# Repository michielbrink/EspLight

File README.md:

# EspLight
https://tkkrlab.nl/wiki/Esp-12_led_strip_controller

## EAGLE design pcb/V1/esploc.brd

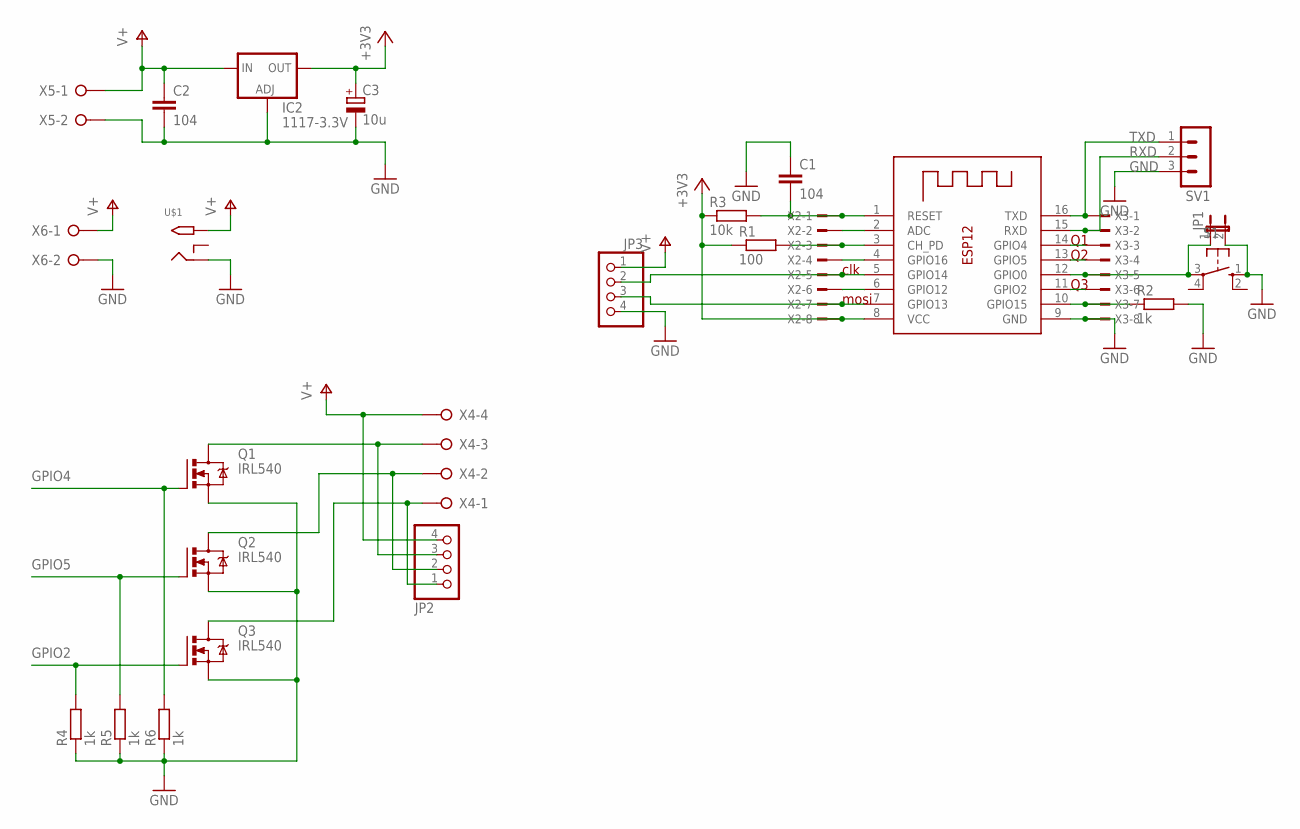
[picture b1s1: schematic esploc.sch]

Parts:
C1, C2: 104; C025_050-025X075
C3: 10u; E2,5-6E
IC2: 1117-3.3V; SOT223
JP1: JP1E; JP1
JP2, JP3: PINHD-1X4; 1X04
Q1, Q2, Q3: IRL540; TO220BV
R1: 100; M0805
R2, R4, R5, R6: 1k; M0805
R3: 10k; M0805
S1: 40-XX; B3F-40XX
SV1: MA03-1
U$1: 2.1MMJACKTHM; PJ-102A
X1: ESP-12
X2, X3: TSW-108-02-S-S
X4: W237-04P; W237-4P
X5, X6: W237-02P; W237-132

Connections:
+3V3: C3.+, IC2.2 (OUT), IC2.4 (OUT), R1.1, R3.1, X1.8 (VCC), X2.8
GND: C1.1, C2.2, C3.-, IC2.1 (ADJ), JP1.2, JP3.4, Q1.S, Q2.S, Q3.S, R2.2, R4.1, R5.1, R6.1, S1.1 (S), SV1.3, U$1.RING, X1.9 (GND), X3.8, X5.2, X6.2
GPIO2: Q3.G, R4.2, X1.11 (GPIO2), X3.6
GPIO4: Q1.G, R6.2, X1.14 (GPIO4), X3.3
GPIO5: Q2.G, R5.2, X1.13 (GPIO5), X3.4
GPIO12: X1.6 (GPIO12), X2.6
GPIO13: JP3.3, X1.7 (GPIO13), X2.7
GPIO14: JP3.2, X1.5 (GPIO14), X2.5
unnamed: C1.2, R3.2, X1.1 (RESET), X2.1
unnamed: R1.2, X1.3 (CH_PD), X2.3
unnamed: R2.1, X1.10 (GPIO15), X3.7
unnamed: X1.4 (GPIO16), X2.4
unnamed: JP1.1, S1.3, X1.12 (GPIO0), X3.5
unnamed: X1.2 (ADC), X2.2
unnamed: JP2.3, Q1.D, X4.3
unnamed: JP2.2, Q2.D, X4.2
unnamed: JP2.1, Q3.D, X4.1
RXD: SV1.2, X1.15 (RXD), X3.2
TXD: SV1.1, X1.16 (TXD), X3.1
V+: C2.1, IC2.3 (IN), JP2.4, JP3.1, U$1.TIP, X4.4, X5.1, X6.1

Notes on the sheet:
clk
mosi

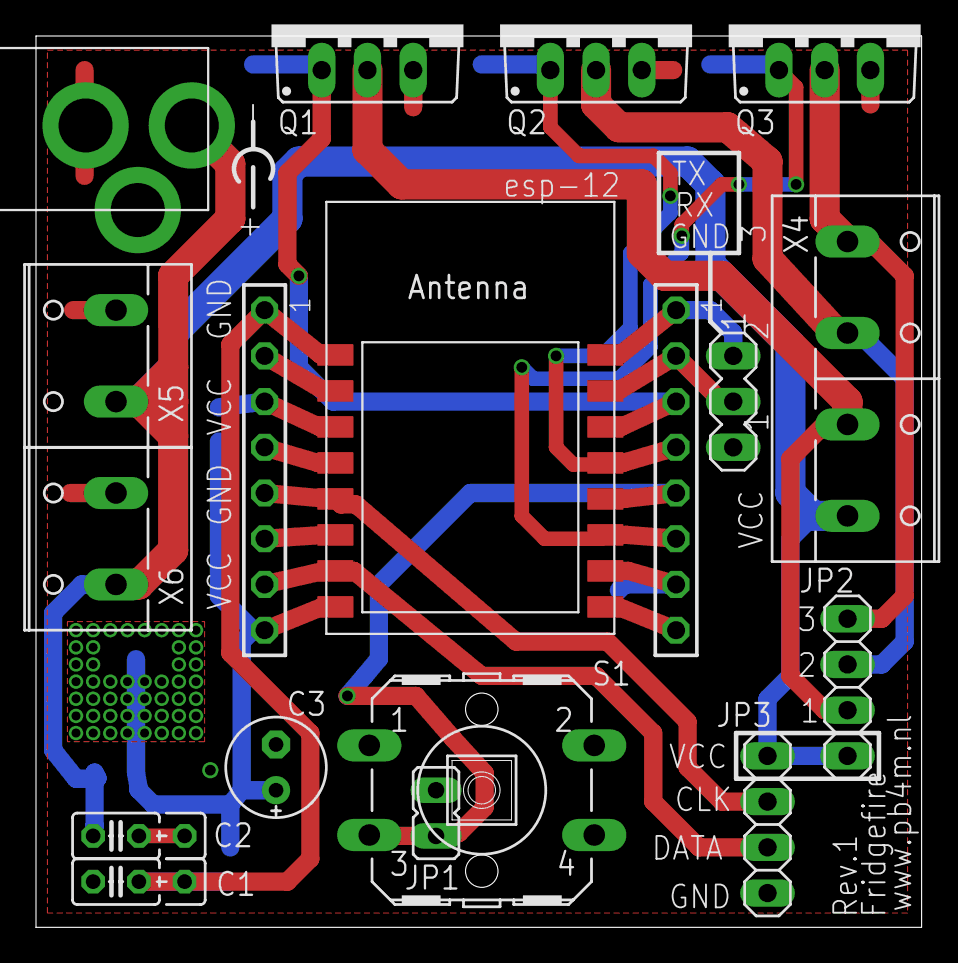
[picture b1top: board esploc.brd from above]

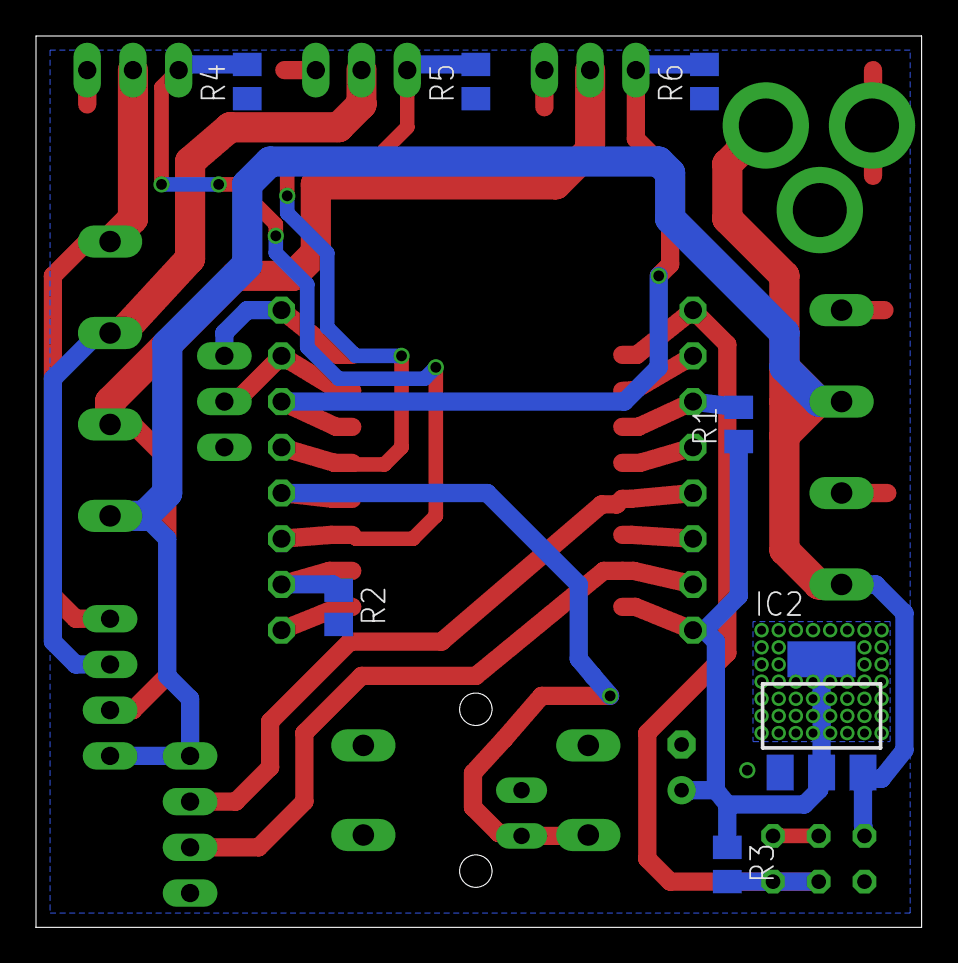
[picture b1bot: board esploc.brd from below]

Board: 2 copper layers, 49.2 x 49.5 mm, 25 parts (7 on the bottom side), 20 nets.

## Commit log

2015-05-19 add files
2015-06-24 change name
2015-06-24 move folder
2016-02-08 project moved
